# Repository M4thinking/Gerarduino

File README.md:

# Gerarduino
Gerarduino robot-racer

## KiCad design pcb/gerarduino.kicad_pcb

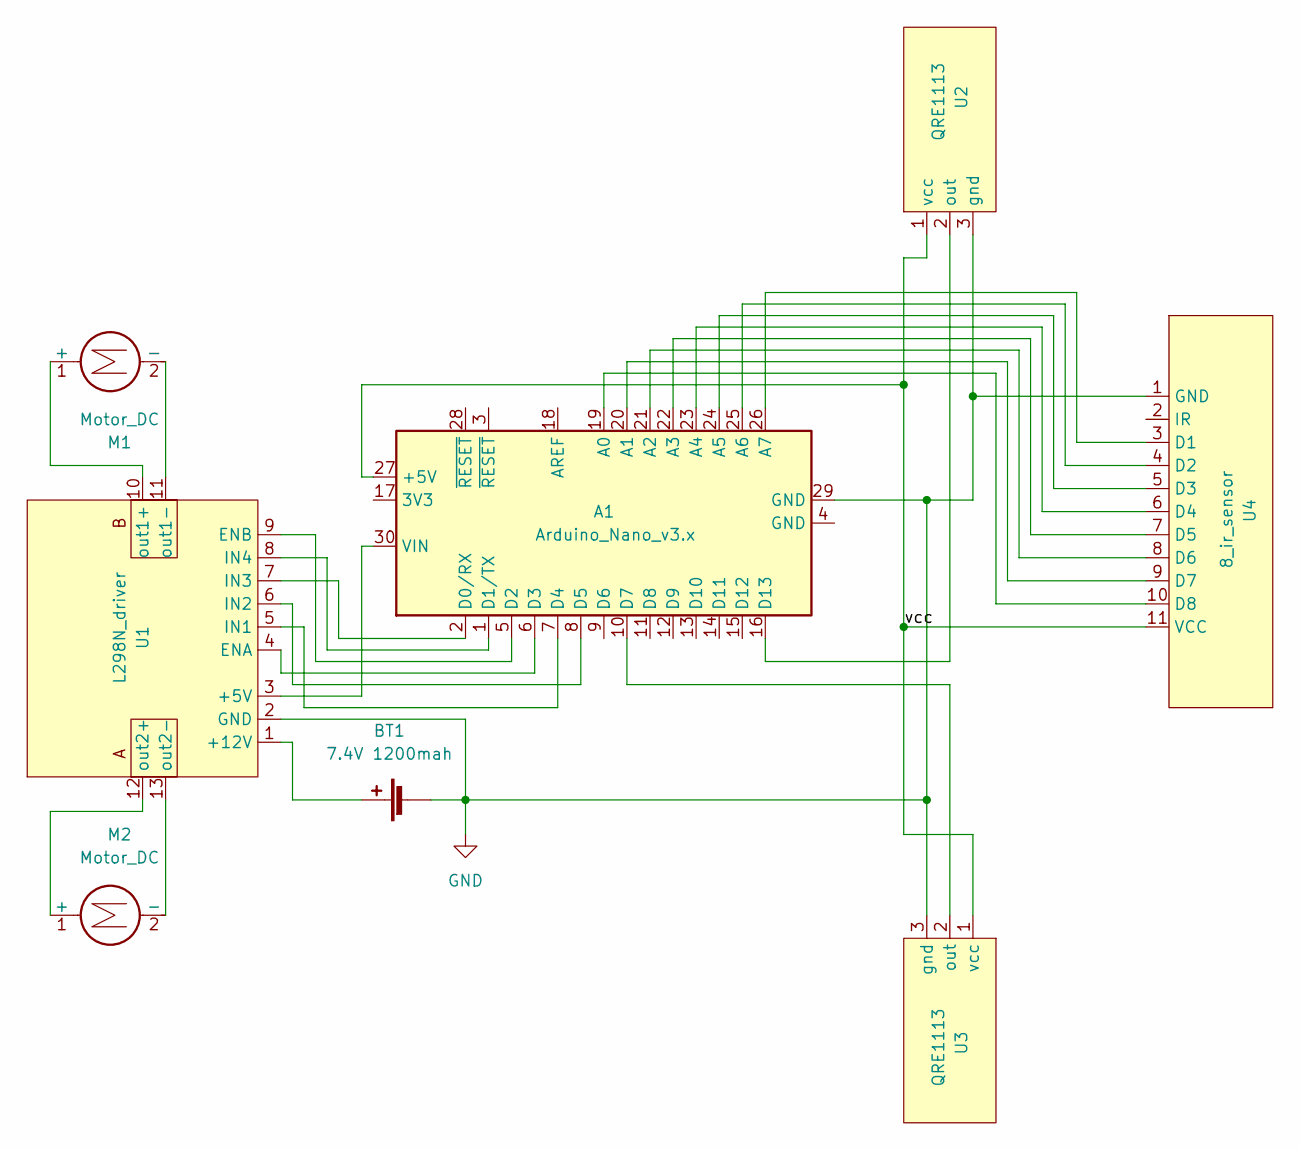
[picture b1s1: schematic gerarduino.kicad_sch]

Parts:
A1: Arduino_Nano_v3.x; Arduino_Nano
BT1: 7.4V 1200mah; dc_motor_th
M1, M2: Motor_DC; dc_motor_th
U1: L298N_driver
U2, U3: QRE1113; SENSOR_QTR-1A_REFLECTANCE_SENSOR
U4: 8_ir_sensor

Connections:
/vcc: A1.27 (+5V), U2.1 (vcc), U3.1 (vcc), U4.11 (VCC)
GND: A1.29 (GND), BT1.2 (-), U1.2 (GND), U2.3 (gnd), U3.3 (gnd), U4.1 (GND)
unnamed: A1.1 (D1/TX), U1.8 (IN4)
unnamed: A1.2 (D0/RX), U1.7 (IN3)
unnamed: A1.5 (D2), U1.9 (ENB)
unnamed: A1.6 (D3), U1.4 (ENA)
unnamed: A1.7 (D4), U1.5 (IN1)
unnamed: A1.8 (D5), U1.6 (IN2)
unnamed: A1.10 (D7), U3.2 (out)
unnamed: A1.16 (D13), U2.2 (out)
unnamed: A1.19 (A0), U4.10 (D8)
unnamed: A1.20 (A1), U4.9 (D7)
unnamed: A1.21 (A2), U4.8 (D6)
unnamed: A1.22 (A3), U4.7 (D5)
unnamed: A1.23 (A4), U4.6 (D4)
unnamed: A1.24 (A5), U4.5 (D3)
unnamed: A1.25 (A6), U4.4 (D2)
unnamed: A1.26 (A7), U4.3 (D1)
unnamed: A1.30 (VIN), U1.3 (+5V)
unnamed: BT1.1 (+), U1.1 (+12V)
unnamed: M1.1 (+), U1.10 (out1+)
unnamed: M1.2 (-), U1.11 (out1-)
unnamed: M2.1 (+), U1.12 (out2+)
unnamed: M2.2 (-), U1.13 (out2-)

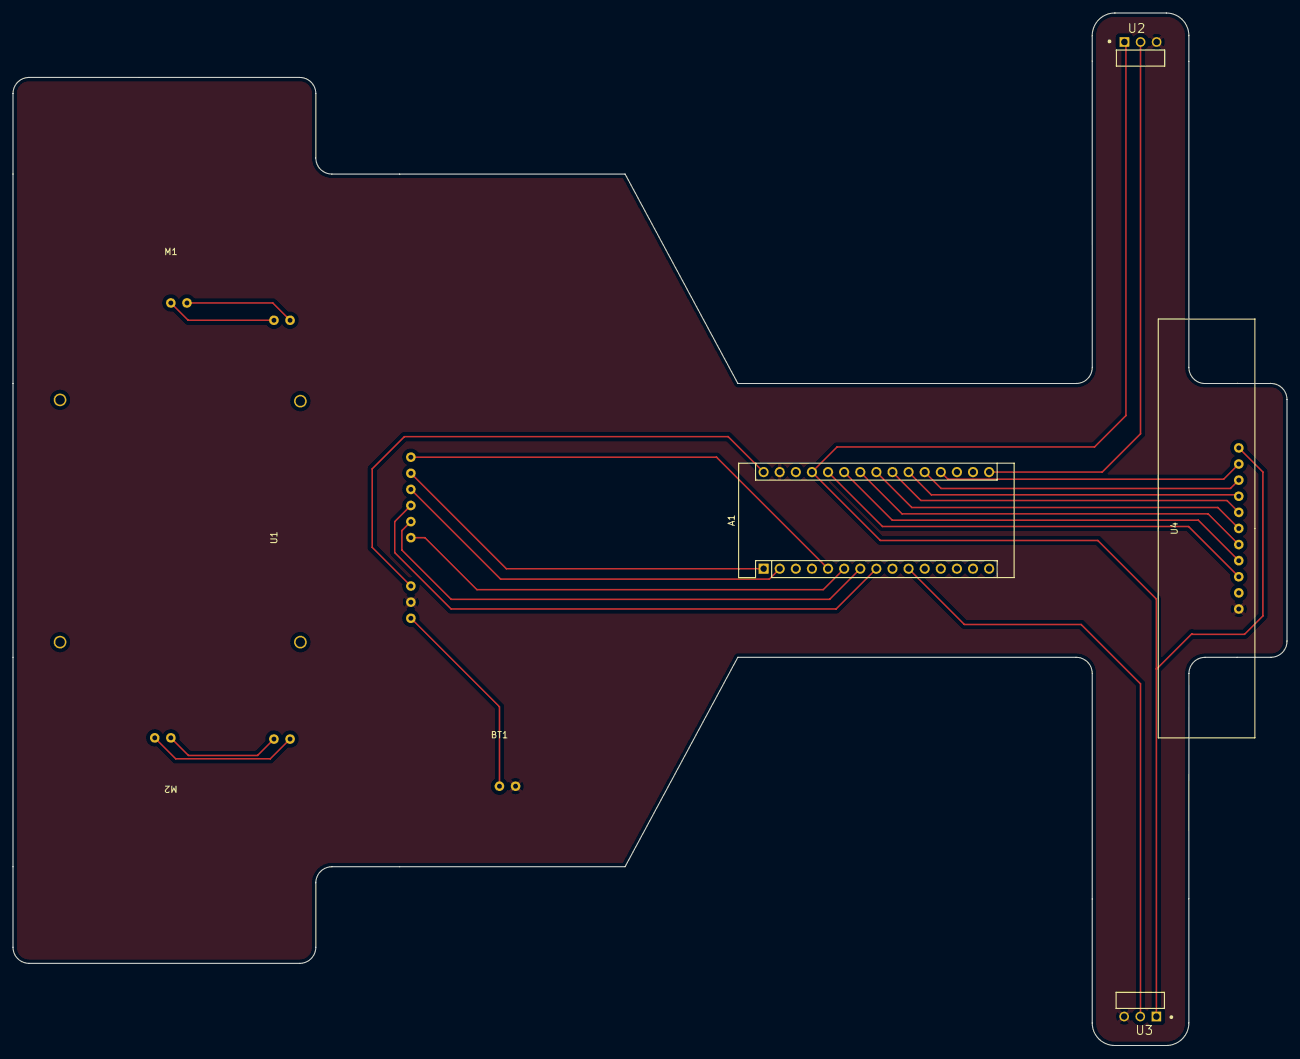
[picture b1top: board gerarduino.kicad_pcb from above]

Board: 2 copper layers, 200.9 x 162.8 mm, 8 parts (0 on the bottom side), 24 nets.

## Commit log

2022-09-21 code for 2 motors with IR sensors
2022-09-21 Iteración con gerarduino humilde. Solo se mueve hacia los lados
2022-09-30 se agrega control PID con manejo de sensores IR
2022-10-05 Control PD incorporado y mejor diseño para la velocidad
2022-10-05 PID funcional con error en estado estacionario
2022-10-12 pruebas pid
2022-11-03 reestructuracion y se agregan sensores laterales
2022-11-04 Ajuste de código
2022-11-05 Cambios generales
2022-11-05 Tests
2022-11-06 Gerardos's first steps
2022-11-09 GerarduinoV05
2022-11-10 cambio de nombre de carpetas de version y nuevo codigo para motor 1500rpm
2022-11-29 PCB en KiCAD
